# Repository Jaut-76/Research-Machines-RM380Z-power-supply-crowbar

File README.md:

# Research Machines RM380Z power supply crowbar
 This is the kicad project for the power protection circuit for a research machines RM380 as the original supply has no protection to the computer cards.

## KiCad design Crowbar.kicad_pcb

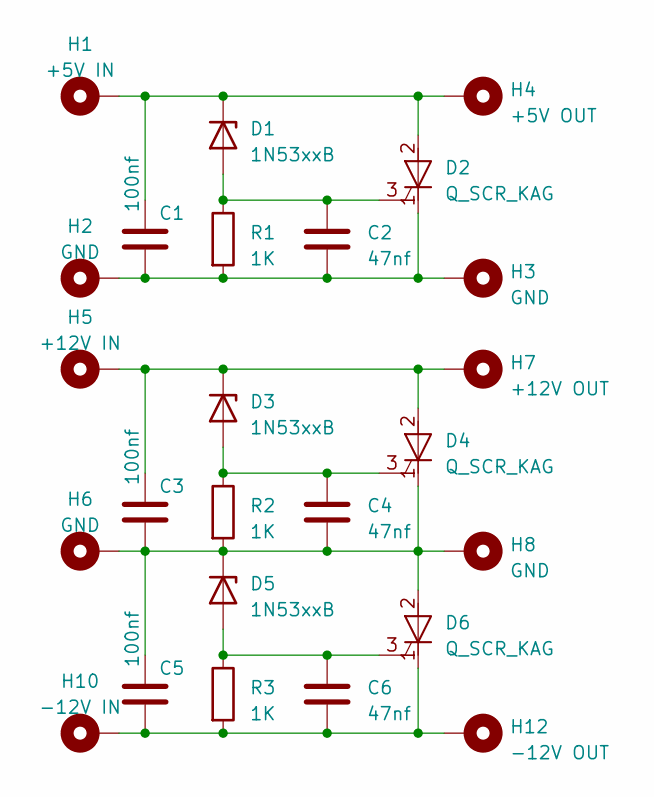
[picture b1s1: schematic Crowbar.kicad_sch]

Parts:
C1, C3, C5: 100nf; C_Axial_L5.1mm_D3.1mm_P7.50mm_Horizontal
C2, C4, C6: 47nf; C_Axial_L3.8mm_D2.6mm_P7.50mm_Horizontal
D1, D3, D5: 1N53xxB; D_DO-201_P15.24mm_Horizontal
D2, D4, D6: Q_SCR_KAG; TO-220-3_Horizontal_TabDown
H1: +5V IN; PinHeader_1x01_P2.54mm_Vertical
H2, H3, H6, H8: GND; PinHeader_1x01_P2.54mm_Vertical
H4: +5V OUT; PinHeader_1x01_P2.54mm_Vertical
H5: +12V IN; PinHeader_1x01_P2.54mm_Vertical
H7: +12V OUT; PinHeader_1x01_P2.54mm_Vertical
H10: -12V IN; PinHeader_1x01_P2.54mm_Vertical
H12: -12V OUT; PinHeader_1x01_P2.54mm_Vertical
R1, R2, R3: 1K; R_Axial_DIN0207_L6.3mm_D2.5mm_P5.08mm_Vertical

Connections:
unnamed: C2.1, D1.2 (A), D2.3 (G), R1.1
unnamed: C1.1, D1.1 (K), D2.2 (A), H1.1, H4.1
unnamed: C1.2, C2.2, D2.1 (K), H2.1, H3.1, R1.2
unnamed: C4.1, D3.2 (A), D4.3 (G), R2.1
unnamed: C3.1, D3.1 (K), D4.2 (A), H5.1, H7.1
unnamed: C3.2, C4.2, C5.1, D4.1 (K), D5.1 (K), D6.2 (A), H6.1, H8.1, R2.2
unnamed: C6.1, D5.2 (A), D6.3 (G), R3.1
unnamed: C5.2, C6.2, D6.1 (K), H10.1, H12.1, R3.2

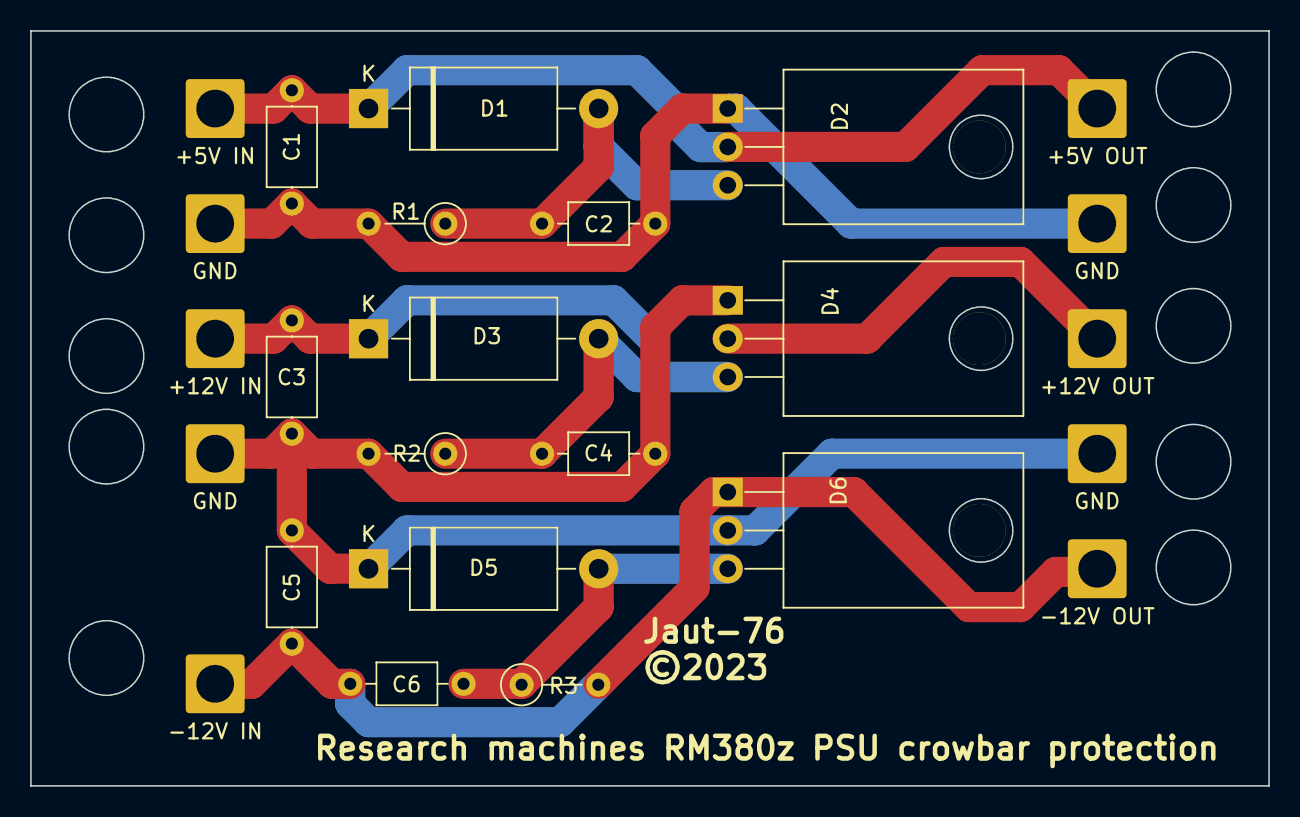
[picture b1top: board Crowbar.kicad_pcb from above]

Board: 2 copper layers, 82.0 x 50.0 mm, 25 parts (0 on the bottom side), 8 nets.

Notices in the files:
Crowbar.kicad_pcb:
©2023
